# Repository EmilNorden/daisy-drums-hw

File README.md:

## Daisy Drums Hardware

This repository contains the kicad files for the PCB used in my project "Daisy Drums"

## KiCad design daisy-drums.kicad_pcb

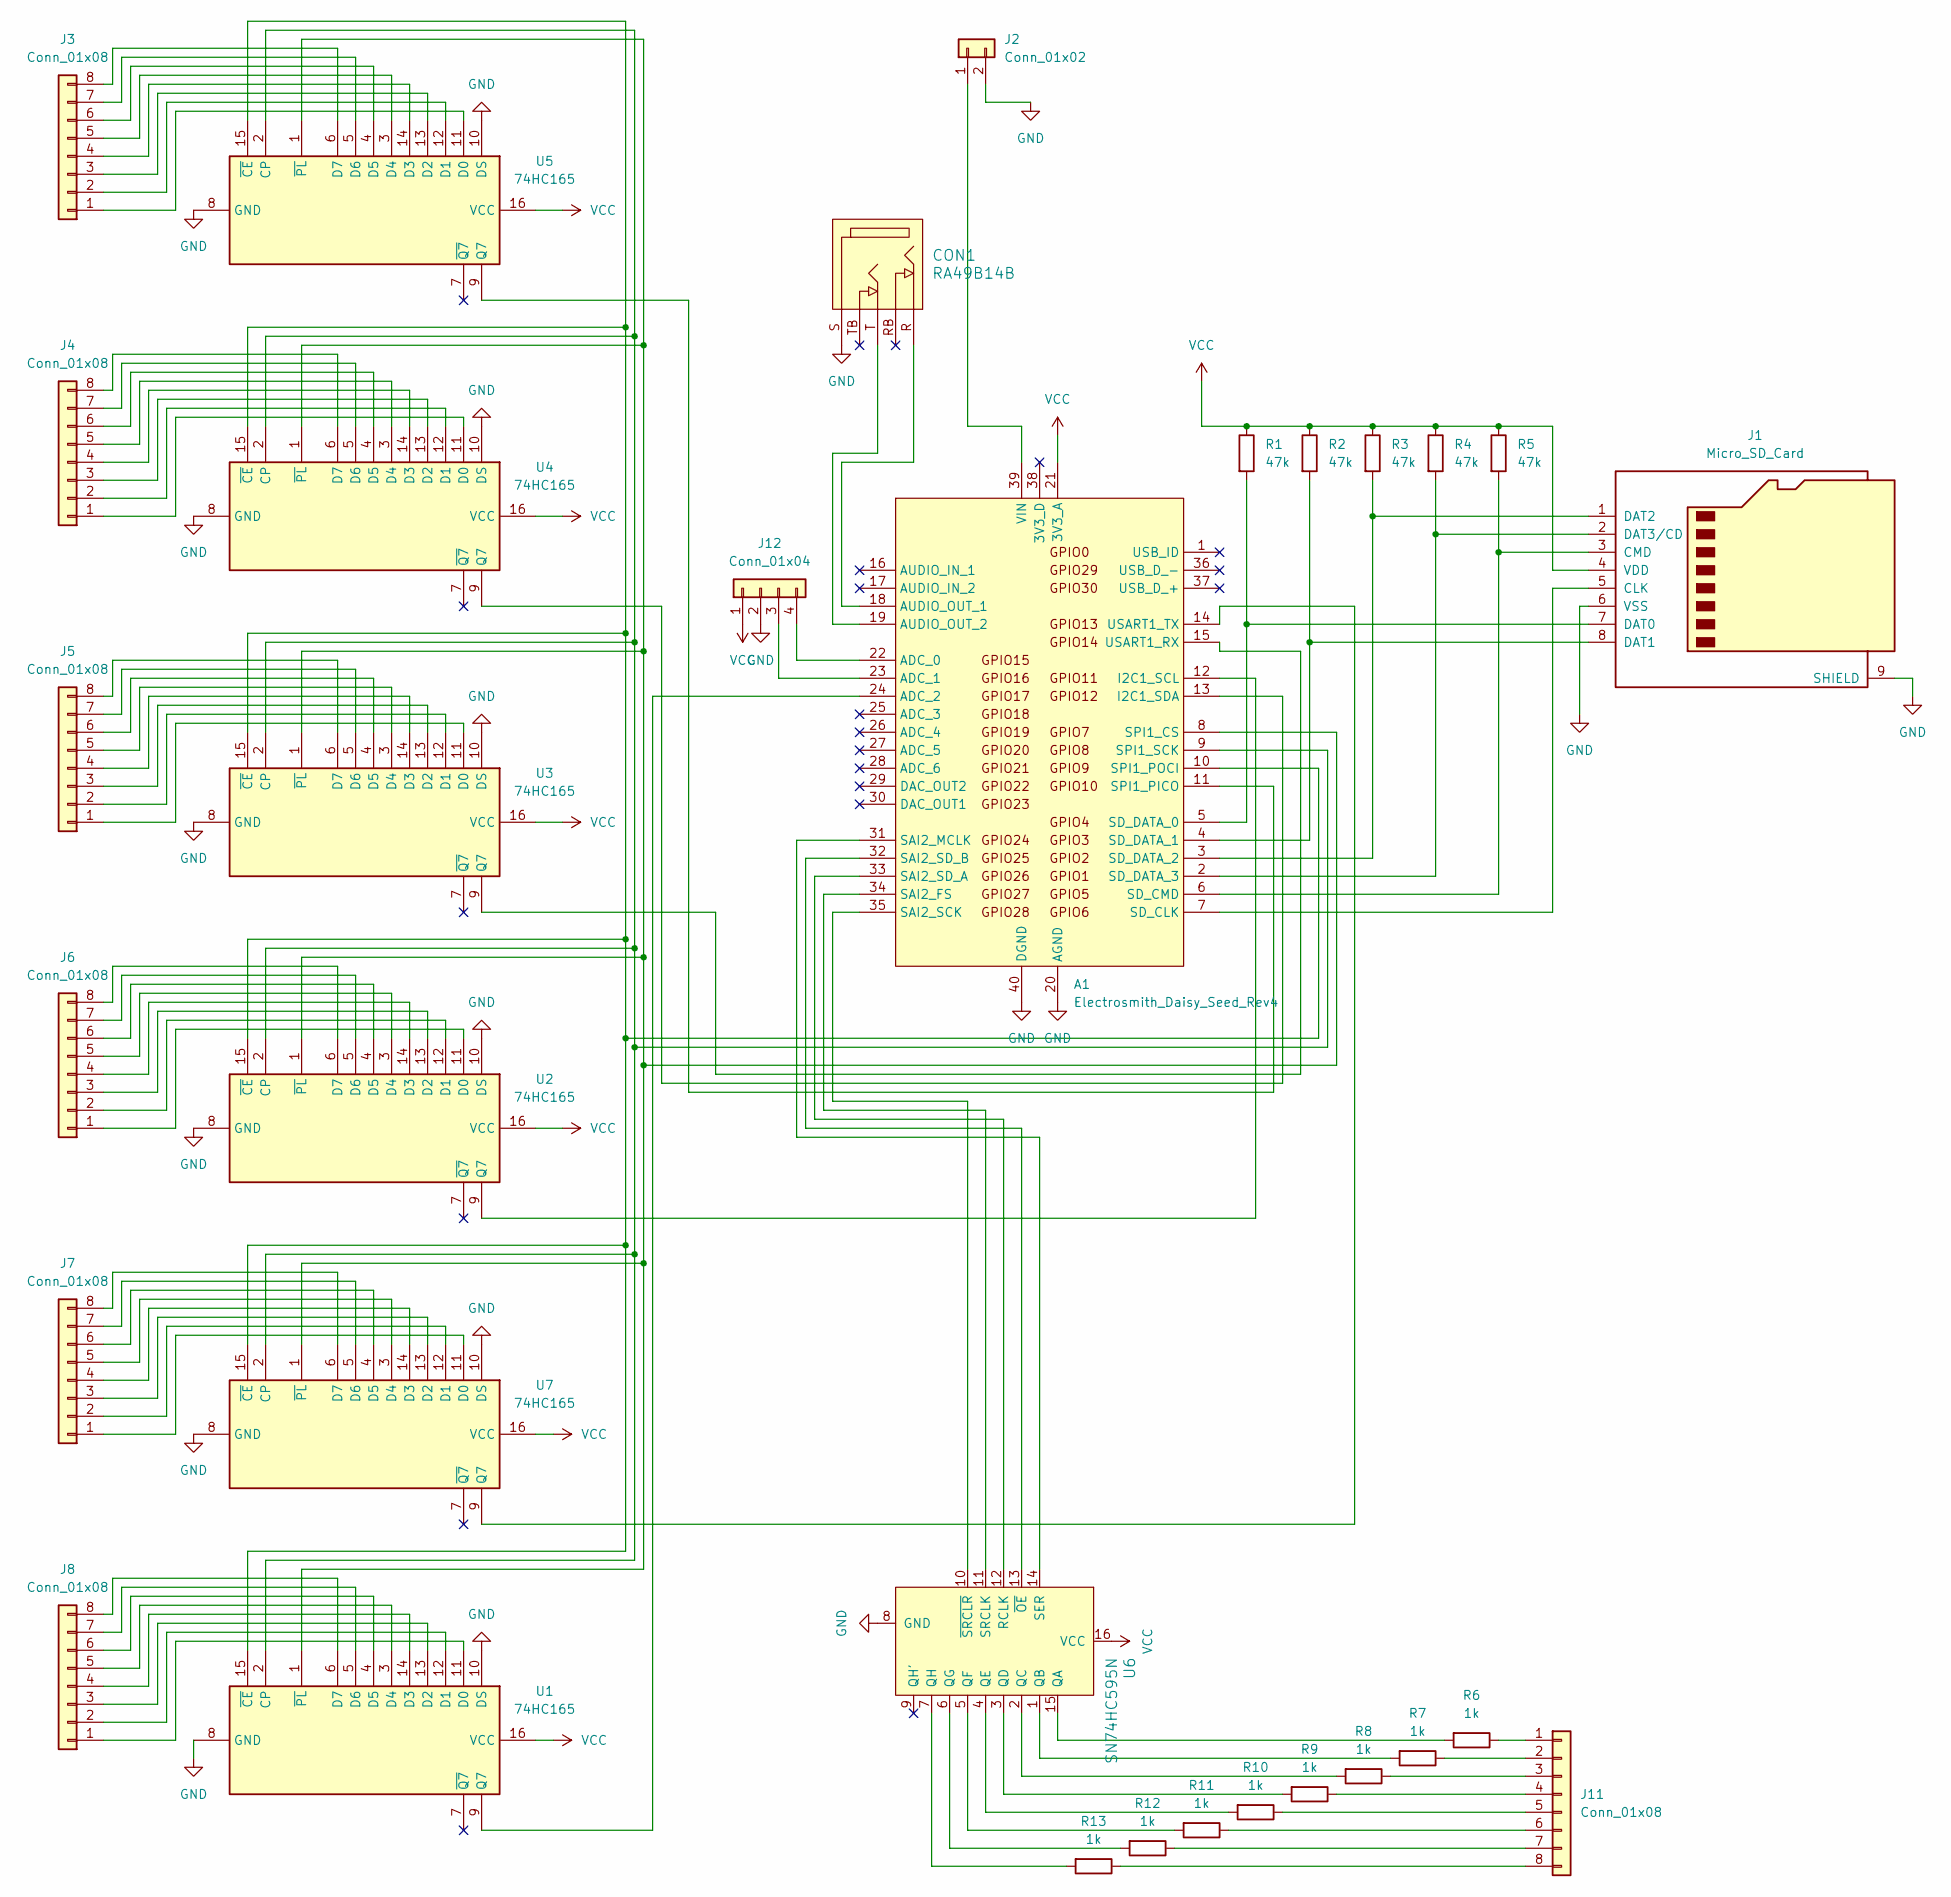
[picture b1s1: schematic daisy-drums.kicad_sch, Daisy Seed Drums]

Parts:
A1: Electrosmith_Daisy_Seed_Rev4; Electrosmith_Daisy_Seed
CON1: RA49B14B; Headphone_Jack_6.35mm_RA49B14B; MPN RA49B14B; Digi-Key_PN SC2030-ND
J1: Micro_SD_Card; microSD_HC_Hirose_DM3D-SF
J2: Conn_01x02; Molex_KK-254_AE-6410-02A_1x02_P2.54mm_Vertical
J3, J4, J5, J6, J7, J8, J11: Conn_01x08; Molex_KK-254_AE-6410-08A_1x08_P2.54mm_Vertical
J12: Conn_01x04; Molex_KK-254_AE-6410-04A_1x04_P2.54mm_Vertical
R1, R2, R3, R4, R5: 47k; R_0805_2012Metric
R6, R7, R8, R9, R10, R11, R12, R13: 1k; R_1206_3216Metric
U1, U2, U3, U4, U5, U7: 74HC165; SOIC-16_3.9x9.9mm_P1.27mm
U6: SN74HC595N; SOP-16_3.9x9.9mm_P1.27mm; MPN SN74HC595N; Digi-Key_PN 296-1600-5-ND

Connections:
GND: A1.20 (AGND), A1.40 (DGND), CON1.S, J1.6 (VSS), J1.9 (SHIELD), J2.2, J12.2, U1.8 (GND), U1.10 (DS), U2.8 (GND), U2.10 (DS), U3.8 (GND), U3.10 (DS), U4.8 (GND), U4.10 (DS), U5.8 (GND), U5.10 (DS), U6.8 (GND), U7.8 (GND), U7.10 (DS)
unnamed: A1.22 (ADC_0), J12.4
unnamed: A1.23 (ADC_1), J12.3
unnamed: A1.24 (ADC_2), U1.9 (Q7)
unnamed: A1.18 (AUDIO_OUT_1), CON1.R
unnamed: A1.19 (AUDIO_OUT_2), CON1.T
unnamed: A1.12 (I2C1_SCL), U2.9 (Q7)
unnamed: A1.13 (I2C1_SDA), U4.9 (Q7)
unnamed: A1.34 (SAI2_FS), U6.11 (SRCLK)
unnamed: A1.31 (SAI2_MCLK), U6.14 (SER)
unnamed: A1.35 (SAI2_SCK), U6.10 (~SRCLR)
unnamed: A1.33 (SAI2_SD_A), U6.12 (RCLK)
unnamed: A1.32 (SAI2_SD_B), U6.13 (~OE)
unnamed: A1.7 (SD_CLK), J1.5 (CLK)
unnamed: A1.6 (SD_CMD), J1.3 (CMD), R5.2
unnamed: A1.5 (SD_DATA_0), J1.7 (DAT0), R1.2
unnamed: A1.4 (SD_DATA_1), J1.8 (DAT1), R2.2
unnamed: A1.3 (SD_DATA_2), J1.1 (DAT2), R3.2
unnamed: A1.2 (SD_DATA_3), J1.2 (DAT3/CD), R4.2
unnamed: A1.8 (SPI1_CS), U1.1 (~PL), U2.1 (~PL), U3.1 (~PL), U4.1 (~PL), U5.1 (~PL), U7.1 (~PL)
unnamed: A1.11 (SPI1_PICO), U5.9 (Q7)
unnamed: A1.10 (SPI1_POCI), U1.15 (~CE), U2.15 (~CE), U3.15 (~CE), U4.15 (~CE), U5.15 (~CE), U7.15 (~CE)
unnamed: A1.9 (SPI1_SCK), U1.2 (CP), U2.2 (CP), U3.2 (CP), U4.2 (CP), U5.2 (CP), U7.2 (CP)
unnamed: A1.15 (USART1_RX), U3.9 (Q7)
unnamed: A1.14 (USART1_TX), U7.9 (Q7)
unnamed: A1.39 (VIN), J2.1
unnamed: J3.1, U5.11 (D0)
unnamed: J3.2, U5.12 (D1)
unnamed: J3.3, U5.13 (D2)
unnamed: J3.4, U5.14 (D3)
unnamed: J3.5, U5.3 (D4)
unnamed: J3.6, U5.4 (D5)
unnamed: J3.7, U5.5 (D6)
unnamed: J3.8, U5.6 (D7)
unnamed: J4.1, U4.11 (D0)
unnamed: J4.2, U4.12 (D1)
unnamed: J4.3, U4.13 (D2)
unnamed: J4.4, U4.14 (D3)
unnamed: J4.5, U4.3 (D4)
unnamed: J4.6, U4.4 (D5)
unnamed: J4.7, U4.5 (D6)
unnamed: J4.8, U4.6 (D7)
unnamed: J5.1, U3.11 (D0)
unnamed: J5.2, U3.12 (D1)
unnamed: J5.3, U3.13 (D2)
unnamed: J5.4, U3.14 (D3)
unnamed: J5.5, U3.3 (D4)
unnamed: J5.6, U3.4 (D5)
unnamed: J5.7, U3.5 (D6)
unnamed: J5.8, U3.6 (D7)
unnamed: J6.1, U2.11 (D0)
unnamed: J6.2, U2.12 (D1)
unnamed: J6.3, U2.13 (D2)
unnamed: J6.4, U2.14 (D3)
unnamed: J6.5, U2.3 (D4)
unnamed: J6.6, U2.4 (D5)
unnamed: J6.7, U2.5 (D6)
unnamed: J6.8, U2.6 (D7)
unnamed: J7.1, U7.11 (D0)
unnamed: J7.2, U7.12 (D1)
unnamed: J7.3, U7.13 (D2)
unnamed: J7.4, U7.14 (D3)
unnamed: J7.5, U7.3 (D4)
unnamed: J7.6, U7.4 (D5)
unnamed: J7.7, U7.5 (D6)
unnamed: J7.8, U7.6 (D7)
unnamed: J8.1, U1.11 (D0)
unnamed: J8.2, U1.12 (D1)
unnamed: J8.3, U1.13 (D2)
unnamed: J8.4, U1.14 (D3)
unnamed: J8.5, U1.3 (D4)
unnamed: J8.6, U1.4 (D5)
unnamed: J8.7, U1.5 (D6)
unnamed: J8.8, U1.6 (D7)
unnamed: J11.1, R6.1
unnamed: J11.2, R7.1
unnamed: J11.3, R8.1
unnamed: J11.4, R9.1
unnamed: J11.5, R10.1
unnamed: J11.6, R11.1
unnamed: J11.7, R12.1
unnamed: J11.8, R13.1
unnamed: R6.2, U6.15 (QA)
unnamed: R7.2, U6.1 (QB)
unnamed: R8.2, U6.2 (QC)
unnamed: R9.2, U6.3 (QD)
unnamed: R10.2, U6.4 (QE)
unnamed: R11.2, U6.5 (QF)
unnamed: R12.2, U6.6 (QG)
unnamed: R13.2, U6.7 (QH)
VCC: A1.21 (3V3_A), J1.4 (VDD), J12.1, R1.1, R2.1, R3.1, R4.1, R5.1, U1.16 (VCC), U2.16 (VCC), U3.16 (VCC), U4.16 (VCC), U5.16 (VCC), U6.16 (VCC), U7.16 (VCC)

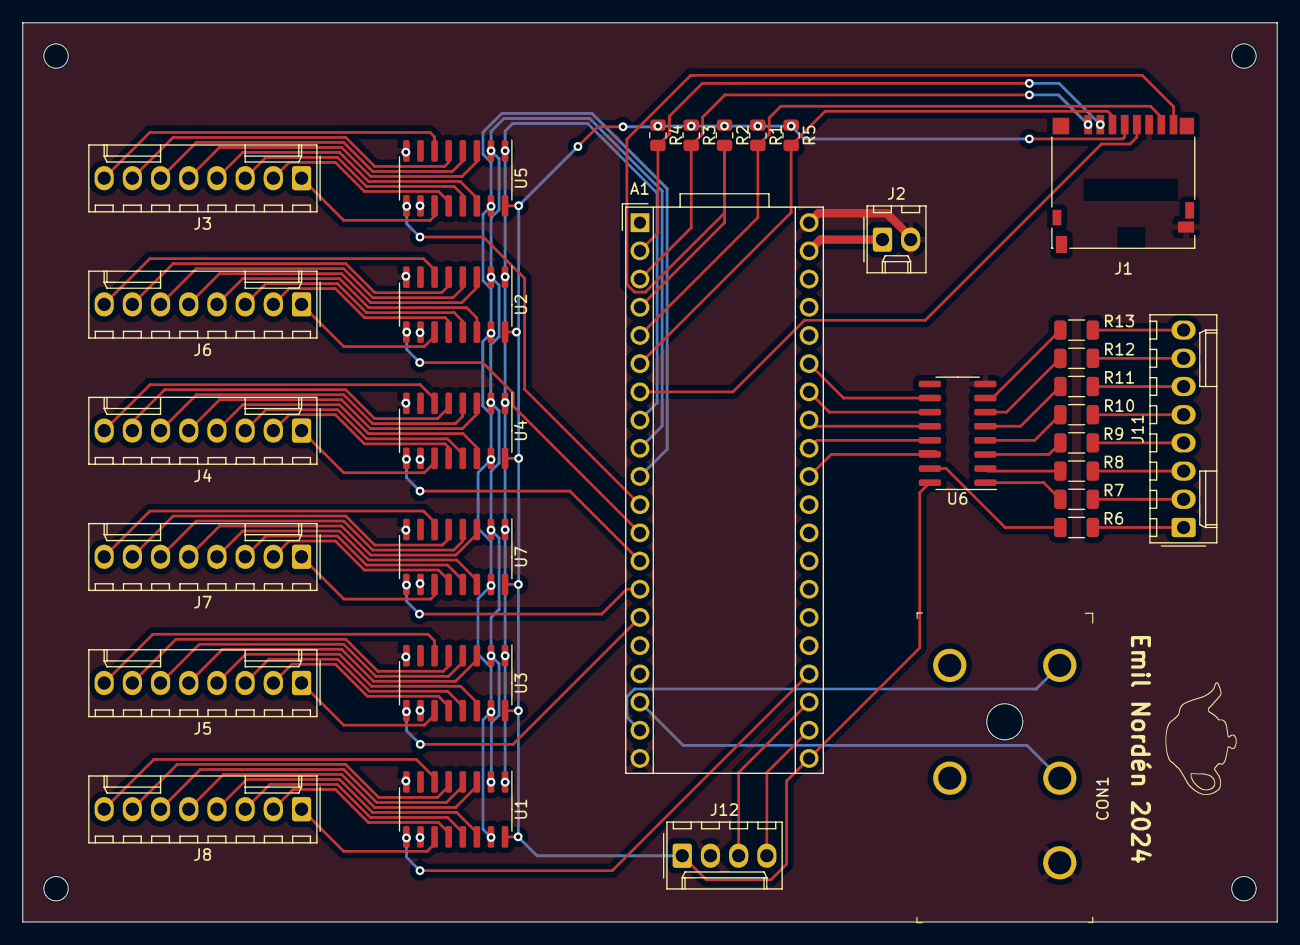
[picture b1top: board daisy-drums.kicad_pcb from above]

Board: 2 copper layers, 113.0 x 81.0 mm, 32 parts (0 on the bottom side), 91 nets.

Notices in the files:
daisy-drums.kicad_pcb:
creativecommons.org/licenses/by/4.0
License: CC BY 4.0
